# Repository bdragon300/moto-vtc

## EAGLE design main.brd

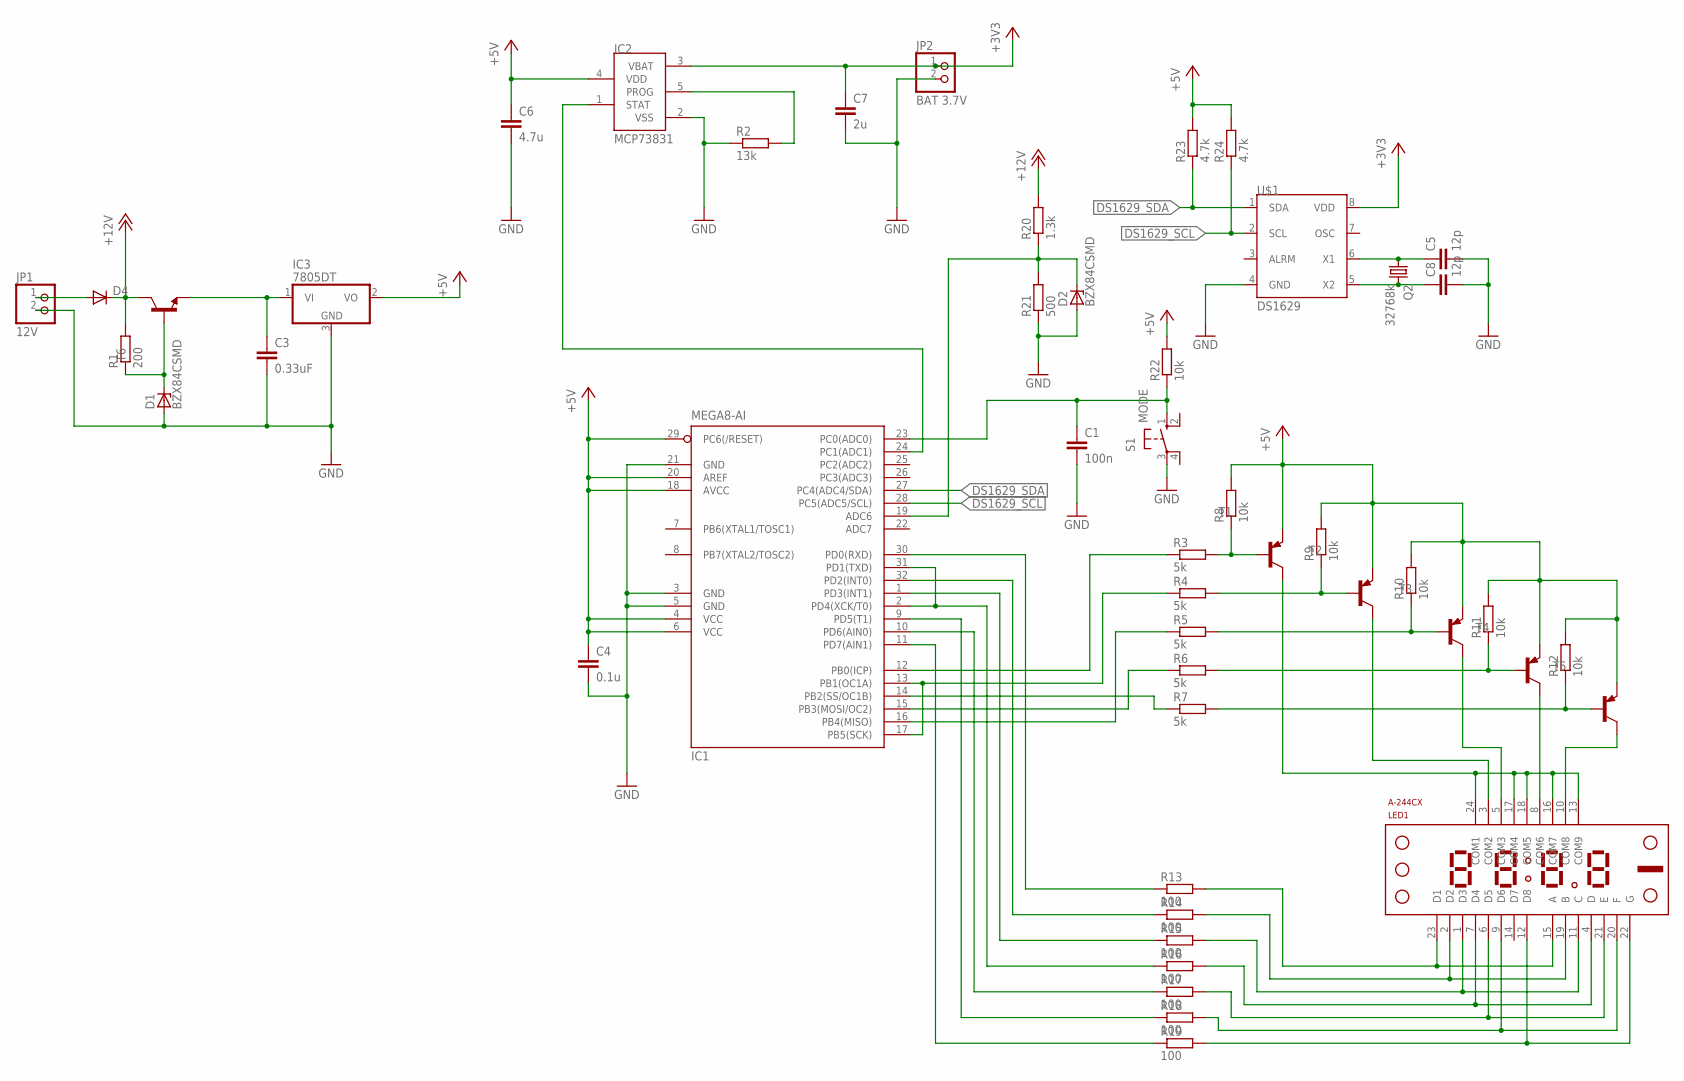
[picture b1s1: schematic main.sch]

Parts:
C1: 100n; C0805
C3: 0.33uF; C1206
C4: 0.1u; C0805
C5, C8: 12p; C0805
C6: 4.7u; C1206
C7: 2u; C1206
D1, D2: BZX84CSMD; TO236
D4: DIODE-D-7.5; D-7.5
IC1: MEGA8-AI; TQFP32-08
IC2: MCP73831; SOT23-5L
IC3: 7805DT; TO252
JP1: 12V; 1X02
JP2: BAT 3.7V; 1X02
LED1: A-244CX; C/A-244CX
Q2: 32768k; TC26H
R1: 200; M0805
R2: 13k; M0805
R3, R4, R5, R6, R7: 5k; M0805
R8, R9, R10, R11, R12, R22: 10k; M0805
R13, R14, R15, R16, R17, R18, R19: 100; M0805
R20: 1.3k; M0805
R21: 500; M0805
R23, R24: 4.7k; M0805
S1: MODE; B3F-10XX
T1, T2, T3, T4, T5: BC807-25-PNP-SOT23-BEC; SOT23-BEC
T6: -NPN-SOT23-EBC; SOT23-EBC
U$1: DS1629; SOIC-8

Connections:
+5V: C4.1, C6.1, IC1.4 (VCC), IC1.6 (VCC), IC1.18 (AVCC), IC1.20 (AREF), IC1.29 (PC6(/RESET)), IC2.4 (VDD), IC3.2 (VO), R8.2, R9.2, R10.2, R11.2, R12.2, R22.2, R23.2, R24.2, T1.E, T2.E, T3.E, T4.E, T5.E
+12V: D4.C, R1.2, R20.2, T6.C
DS1629_SCL: IC1.28 (PC5(ADC5/SCL)), R24.1, U$1.2 (SCL)
DS1629_SDA: IC1.27 (PC4(ADC4/SDA)), R23.1, U$1.1 (SDA)
GND: C1.2, C3.2, C4.2, C5.2, C6.2, C7.2, C8.2, D1.A, D2.A, IC1.3 (GND), IC1.5 (GND), IC1.21 (GND), IC2.2 (VSS), IC3.3 (GND), JP1.2, JP2.2, R2.1, R21.1, S1.3, U$1.4 (GND)
unnamed: LED1.2 (D2), LED1.19 (B), R14.2
unnamed: LED1.4 (D), LED1.7 (D4), R16.2
unnamed: D2.C, IC1.19 (ADC6), R20.1, R21.2
unnamed: IC1.24 (PC1(ADC1)), IC2.1 (STAT)
unnamed: D4.A, JP1.1
unnamed: D1.C, R1.1, T6.B
unnamed: C3.1, IC3.1 (VI), T6.E
unnamed: IC2.5 (PROG), R2.2
unnamed: LED1.8 (COM6), T4.C
unnamed: LED1.5 (COM3), T3.C
unnamed: LED1.3 (COM2), T2.C
unnamed: LED1.13 (COM9), LED1.16 (COM7), LED1.17 (COM4), LED1.18 (COM5), LED1.24 (COM1), T1.C
unnamed: R3.2, R8.1, T1.B
unnamed: R4.2, R9.1, T2.B
unnamed: R5.2, R10.1, T3.B
unnamed: R6.2, R11.1, T4.B
unnamed: R7.2, R12.1, T5.B
unnamed: LED1.1 (D3), LED1.11 (C), R15.2
unnamed: IC1.10 (PD6(AIN0)), R17.1
unnamed: IC1.30 (PD0(RXD)), R13.1
unnamed: IC1.32 (PD2(INT0)), R14.1
unnamed: IC1.1 (PD3(INT1)), R15.1
unnamed: IC1.12 (PB0(ICP)), R3.1
unnamed: IC1.13 (PB1(OC1A)), IC1.17 (PB5(SCK)), R4.1
unnamed: IC1.16 (PB4(MISO)), R5.1
unnamed: IC1.15 (PB3(MOSI/OC2)), R6.1
unnamed: IC1.14 (PB2(SS/OC1B)), R7.1
unnamed: C5.1, Q2.1, U$1.6 (X1)
unnamed: C8.1, Q2.2, U$1.5 (X2)
unnamed: IC1.2 (PD4(XCK/T0)), IC1.31 (PD1(TXD)), R16.1
unnamed: LED1.6 (D5), LED1.21 (E), R17.2
unnamed: LED1.9 (D6), LED1.20 (F), R18.2
unnamed: LED1.12 (D8), LED1.22 (G), R19.2
unnamed: LED1.15 (A), LED1.23 (D1), R13.2
unnamed: IC1.9 (PD5(T1)), R18.1
unnamed: IC1.11 (PD7(AIN1)), R19.1
unnamed: LED1.10 (COM8), T5.C
unnamed: C1.1, IC1.23 (PC0(ADC0)), R22.1, S1.1 (S)
VDD: C7.1, IC2.3 (VBAT), JP2.1, U$1.8 (VDD)

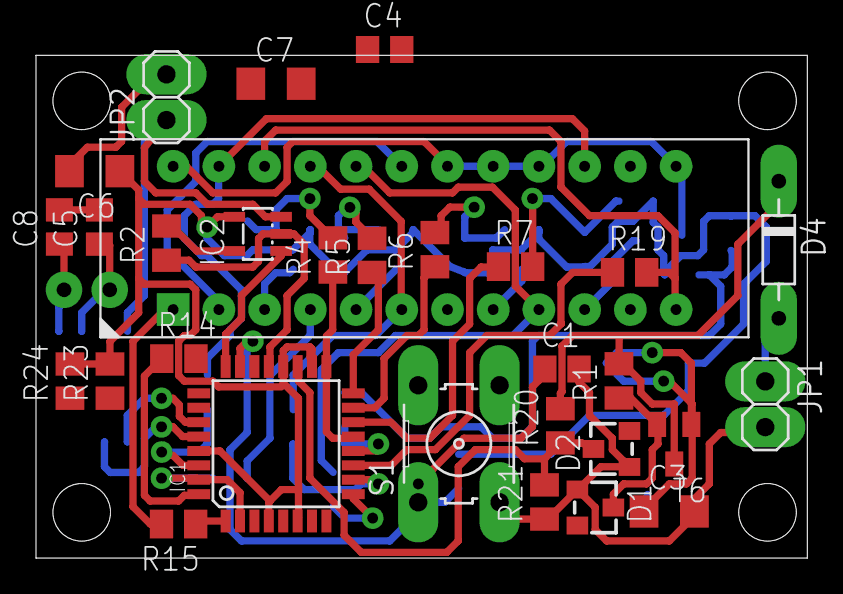
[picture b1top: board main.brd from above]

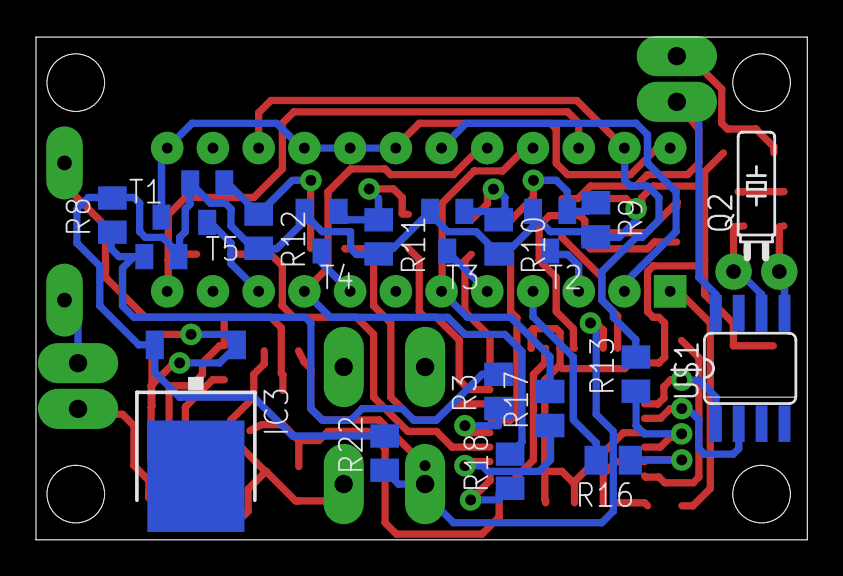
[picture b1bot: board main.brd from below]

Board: 2 copper layers, 42.9 x 27.9 mm, 49 parts (19 on the bottom side), 44 nets.

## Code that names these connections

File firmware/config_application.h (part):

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#define INPUT_PORT                  PORTC;
#define INPUT_PIN                   PINC;
#define INPUT_DDR                   DDRC;
#define VOLTAGE_PIN                 PC6;
#define CHARGE_PIN                  PC1;
#define BUTTON_PIN                  PC0;

/*
 * 7-seg indicator segment pins
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#define DISP_PORT                   PORTD;
#define DISP_PIN                    PIND;
#define DISP_DDR                    DDRD;
#define DISP_A                      PD0;
#define DISP_B                      PD2;
#define DISP_C                      PD3;
#define DISP_D                      PD4;
#define DISP_E                      PD5;
#define DISP_F                      PD6;
#define DISP_G                      PD7;
#define DISP_SEG_MASK \
	_BV(DISP_A)|_BV(DISP_B)|_BV(DISP_C)|_BV(DISP_D)|_BV(DISP_E)|_BV(DISP_F)|_BV(DISP_G)

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#define DISP_COM_PORT               PORTB;
#define DISP_COM_PIN                PINB;
#define DISP_COM_DDR                DDRB;
#define DISP_COM1                   PB1;
#define DISP_COM2                   PB4;
#define DISP_COM3                   PB3;
#define DISP_COM4                   PB2;
#define DISP_COM5                   PB0;
#define DISP_COM_MASK  \
	_BV(DISP_COM1)|_BV(DISP_COM2)|_BV(DISP_COM3)|_BV(DISP_COM4)|_BV(DISP_COM5)

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
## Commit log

2016-03-13 Add gitignore Schematics
2016-03-14 Schematics
2016-03-14 Add datasheets
2016-03-23 Update gitignore
2016-03-24 Atmega8 instead of Atmega16
2016-03-25 Eagle libs
2016-03-26 Schematics, PCB
2016-03-26 Box datasheet
2016-03-26 Elements to buy
2016-03-28 Firmware
2016-04-06 Make display functions
2016-04-07 Fix include guard
2016-04-07 Make user input
2016-04-13 Button noise rejection
2016-04-13 Get voltage function
2016-04-13 Make charge input function
2016-04-13 Correct voltage reading function Work with RTC
2016-04-19 Add eclipse project
2016-04-24 Work with atmega TWI
2016-04-24 Pull-up resistors on TWI bus
2016-04-26 Make TWI hardware interface functions Make indentation in spaces
2016-04-26 Make DS1629 functions
2016-05-09 DS1629 utility functions
2016-05-09 Make temperature and clock manipulation functions
2016-05-10 Rename lib dir
2016-05-10 Many fixes
2016-05-10 Make display_init function
2016-05-12 Minor refactor
2016-05-12 Fix input_tick
2016-05-12 Remove MCU external clock, use internal RC 4 MHz
2016-05-12 Display loop; Utility functions
2016-05-14 Fix input mode swtiching Some refactoring
2016-05-14 Move input configuration
2016-05-14 Refactoring
2016-05-15 Write business logic
2016-05-15 Add input callbacks RELEASE input mode added
2016-05-15 Move sources_data
2016-05-15 Write OS tasks
2016-05-19 Make display disable method Minor fixes
2016-05-19 Bad voltage warning by blinking display
2016-05-19 Make digits can be shadowed
2016-05-19 Prevent sources read in settings mode
2016-05-20 Move display pins to make debug pin
2016-05-20 Add submodules
2016-05-23 Add debug output
2016-05-23 Remove waste files
2016-05-24 Change resistors/capacitors packages from 1206 to 0805
2016-05-25 Swap PB3<=>PB5
2016-05-25 Shift digit common pins Fix digit common pins
2016-05-28 Change input pins
2016-05-28 Schematics and PCB
2016-05-28 Change eclipse settings
2016-05-28 Ignore build directory
2016-06-02 Set Femtoos config
2016-06-19 Make eclipse project as AVR project
2016-06-19 Fix some Femtoos files to be able to build on modern compilers
2016-06-19 gitignore
